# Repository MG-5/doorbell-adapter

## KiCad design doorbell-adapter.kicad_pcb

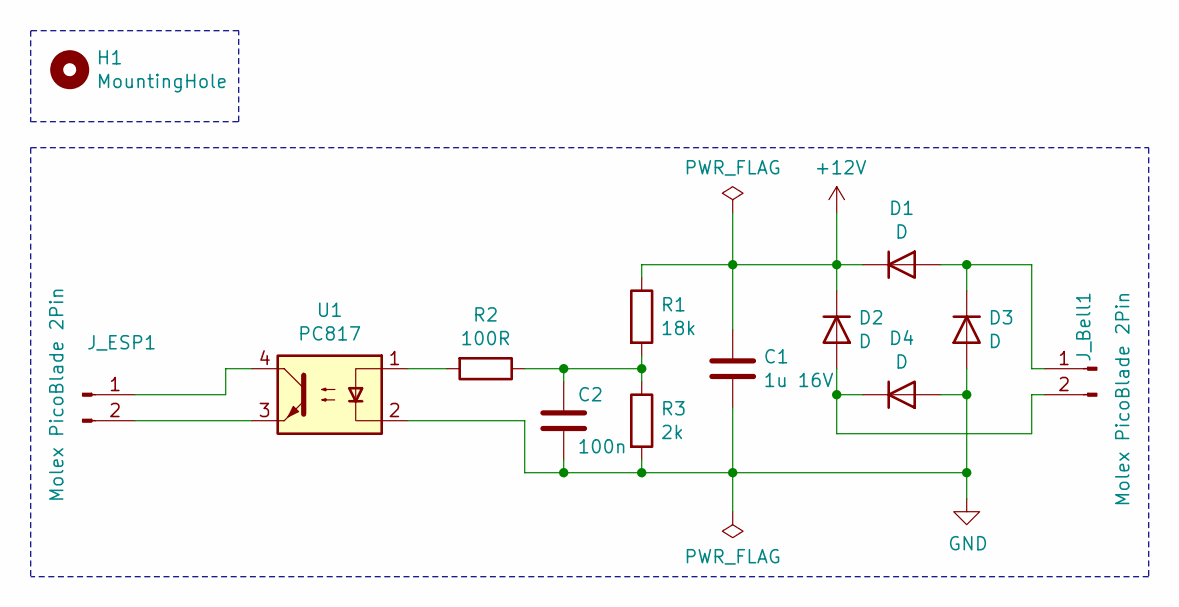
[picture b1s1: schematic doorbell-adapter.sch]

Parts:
C1: 1u 16V; C_0603_1608Metric
C2: 100n; C_0603_1608Metric
D1, D2, D3, D4: D; D_SOD-523
H1: MountingHole; MountingHole_3.2mm_M3_ISO7380_Keepout
J_Bell1: Molex PicoBlade 2Pin; Molex_PicoBlade_53047-0210_1x02_P1.25mm_Vertical
J_ESP1: Molex PicoBlade 2Pin; Molex_PicoBlade_53047-0210_1x02_P1.25mm_Vertical
R1: 18k; R_0603_1608Metric
R2: 100R; R_0603_1608Metric
R3: 2k; R_0603_1608Metric
U1: PC817; DIP-4_W7.62mm

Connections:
+12V: C1.1, D1.1 (K), D2.1 (K), R1.1
GND: C1.2, C2.2, D3.2 (A), D4.2 (A), R3.2, U1.2
unnamed: C2.1, R1.2, R2.1, R3.1
unnamed: D1.2 (A), D3.1 (K), J_Bell1.1
unnamed: D2.2 (A), D4.1 (K), J_Bell1.2
unnamed: J_ESP1.1, U1.4
unnamed: J_ESP1.2, U1.3
unnamed: R2.2, U1.1

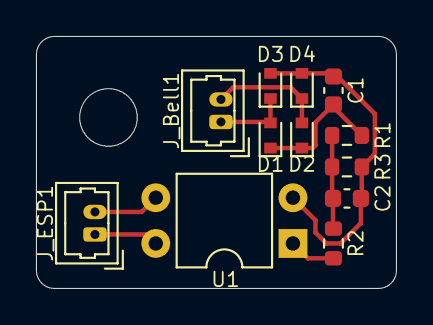
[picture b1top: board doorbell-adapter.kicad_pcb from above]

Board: 2 copper layers, 20.0 x 14.0 mm, 13 parts (0 on the bottom side), 8 nets.

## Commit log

2021-11-25 Add schematic
2021-11-26 Finish PCB
2022-09-29 Create LICENSE
